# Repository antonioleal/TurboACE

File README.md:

# TurboACE

A hardware expansion for the standard Jupiter Ace, built around a Tang Nano 20K FPGA
module. The same module can also be a complete Jupiter Ace on its own (see
[Two builds](#two-builds-expansion-and-standalone)). It adds:

- 512K of paged RAM (64 × 8K pages, two windows);
- a 256×192 hi-res bitmap with 8×1 colour;
- colour text, 32 text pages and 32 character sets;
- HDMI output, with AY sound carried over HDMI;
- SD card storage: programs as tape files, RAM pages, screens and fonts;
- an extension ROM with new Forth words.

Original Jupiter Ace software keeps working.

The design is in [`register-map.md`](register-map.md) and the ROM source in [`rom/`](rom/README.md).
The SD card firmware (for the soft CPU in the FPGA) is in [`firmware/`](firmware/README.md),
and the FPGA design (being written) in [`fpga/`](fpga/README.md).
The tests are in [`test/`](test/).
`./build.sh /path/to/ace.rom` builds everything into `release/`, one folder per build
(`release/standalone/`, `release/expansion/`) with the files written into the module (the
bitstream, with the soft CPU's firmware inside, and the ROM pages for its flash) and a
`LOAD.txt` saying how. It fetches the RISC-V compiler with
`./download_toolchain.sh` the first time; the bitstream needs Gowin EDA in
`toolchain/gowim`. Third-party components and their notices are listed in
[`THIRD-PARTY.md`](THIRD-PARTY.md).

## Two builds: Expansion and Standalone

TurboACE comes as two FPGA bitstreams, made from the same design. Which one the module
runs depends only on what was last written into it:

- **Expansion:** the module sits on a small adapter board plugged into a real Jupiter
  Ace's edge connector. The Ace's own Z80, keyboard and cassette are used; TurboACE
  adds memory, graphics, sound, HDMI and the SD card.
- **Standalone:** no Jupiter Ace is needed. The whole Ace (Z80, memory, keyboard port,
  beeper, 50 Hz interrupt) is inside the FPGA, with a PS/2 keyboard and the SD card as
  the only tape. It runs the same software at the same speed (3.25 MHz, with the stock
  screen-access timing), plus everything TurboACE adds.

|  | Expansion | Standalone |
|---|---|---|
| Needs | a Jupiter Ace, the adapter board, the Tang Nano 20K | the Tang Nano 20K, a PS/2 keyboard and adapter |
| Z80 | the Ace's own | inside the FPGA (T80 core) |
| Keyboard | the Ace's own | PS/2, translated to the Ace's keys (below) |
| Tape | the Ace's cassette port, or the SD card with `SDTAPE` | the SD card only (`SDTAPE` is always on) |
| Display and sound | HDMI (TurboACE's screens and AY sound) | HDMI (screen, AY sound and the beeper) |
| Without `/ace.rom` | the Ace starts on its own ROM, as a stock Ace | `TURBOACE: CANNOT START` on the screen, tries again every second |

**Changing build** means writing the other bitstream into the module through its USB
port with [openFPGALoader](https://github.com/trabucayre/openFPGALoader); nothing else
changes. Both builds also need TurboACE's own ROM pages in the module's flash, written
once (see [`rom/`](rom/README.md)):

```
make program BUILD=standalone ACE_ROM=/path/to/ace.rom   # bitstream and ROM pages
make program-bitstream BUILD=expansion                   # later: change build only
```

`ACE_ROM` is only used to build the ROM pages; the stock ROM itself is not written to
the board. `make load BUILD=...` loads a bitstream until power-off, for testing, and
`FPGALOADER=echo` shows the commands without running them. The targets are in the
top-level [`Makefile`](Makefile).

### Installing the standalone build

**You need:**

- the Tang Nano 20K and a USB-C cable (it powers and programs the module);
- a PS/2 keyboard and the small PS/2 adapter ([The keyboard](#the-keyboard-standalone) below);
- an HDMI display that accepts 720×576 at 50 Hz (most TVs and many monitors);
- a microSD card, FAT32, holding your copy of the stock ROM as `/ace.rom`
  ([The SD card](#the-sd-card) below);
- on the PC: [openFPGALoader](https://github.com/trabucayre/openFPGALoader).

**The files** are in `release/standalone/`, made by `./build.sh /path/to/ace.rom` (it
needs Gowin EDA in `toolchain/gowim` for the bitstream; see [`INDEX.md`](INDEX.md)):
`turboace-standalone.fs` (the bitstream) and `turboace-flash.bin` (TurboACE's ROM pages).
Its `LOAD.txt` has the same commands as below.

**Steps:**

1. **Prepare the card:** format it FAT32 and copy the stock ROM to it as `/ace.rom`.
   Programs go in `/programs`.
2. **Wire the keyboard** through the level shifter to FPGA pins **73** (clock) and
   **74** (data), the first two pins of the module's left header at the USB end, with
   5 V and ground, as in the table below. Plug in the display.
3. **Connect the module** to the PC by USB. Check that openFPGALoader sees it:
   ```
   openFPGALoader --detect -b tangnano20k
   ```
   If it says it cannot open the device, your user may not have access to the USB
   port: run the command as root once, or allow it permanently with a udev rule
   (the module's USB ID is `0403:6010`), then unplug and replug the module:
   ```
   # /etc/udev/rules.d/99-tangnano20k.rules
   SUBSYSTEM=="usb", ATTRS{idVendor}=="0403", ATTRS{idProduct}=="6010", MODE="0666"
   ```
   ```
   udevadm control --reload-rules && udevadm trigger
   ```
4. **Write TurboACE's ROM pages** into the module's flash (once; both builds use them):
   ```
   make program-rom ACE_ROM=/path/to/ace.rom
   ```
   or, from `release/standalone/`:
   `openFPGALoader -b tangnano20k --external-flash -o 0x500000 turboace-flash.bin`
5. **Try the bitstream** without writing it to flash; it is lost at power-off:
   ```
   make load BUILD=standalone
   ```
   With the card in, the Jupiter Ace's screen and prompt appear on the display within
   a second.
6. **Write it to flash** so the module starts as a Jupiter Ace at every power-up:
   ```
   make program-bitstream BUILD=standalone
   ```
   or, from `release/standalone/`: `openFPGALoader -b tangnano20k -f turboace-standalone.fs`

`make program BUILD=standalone ACE_ROM=/path/to/ace.rom` does steps 4 and 6 together.
Button **S1** on the module resets everything (as a power-up); **Ctrl + Alt + Del**
resets only the Ace.

**The module's LEDs** (on when lit) show how far it got:

| LED (pin) | On means |
|---|---|
| 0 (15) | the Z80 is running |
| 1 (16) | the ROM is loaded (from `/ace.rom` and the flash) |
| 2 (17) | the SD card has been used |
| 3 (18) | the picture fell behind (should never light) |

**If something is wrong:**

- *No picture:* check the display accepts 720×576 at 50 Hz. If LEDs 0 and 1 are on, the
  Ace is running and the fault is in the HDMI output; this first bitstream has not yet
  been tried on a board, so please report it.
- *`TURBOACE: CANNOT START` on the screen:* `/ace.rom` is missing or not the stock ROM
  (it must be 8,192 bytes, MD5 `db6efdfd82cebdfbb493d85b1a5efc3c`). TurboACE tries again
  every second, so fixing the card is enough.
- *LED 1 stays off:* the card is not read: check it is FAT32 and fully inserted, and that
  step 4 was done.
- *The keyboard does nothing:* check the level shifter's wiring and its 5 V and 3.3 V
  supplies; data and clock must not be swapped.

### The SD card

**The card must hold `/ace.rom`**, your own copy of the stock Jupiter Ace ROM (8,192
bytes, MD5 `db6efdfd82cebdfbb493d85b1a5efc3c`). TurboACE does not include it: at power-up
it reads it from the card, checks it, and builds its ROM from it. If it is missing or
different, the standalone build says why on the screen and starts as soon as the card is
right; the expansion leaves the Ace to start on its own ROM, as a plain stock Ace.

The SD words start in the folder `/programs`; see [SD card](#sd-card) below.

### The keyboard (standalone)

A PC keyboard with a PS/2 connector plugs into a small PS/2 adapter next to the module.
The keyboard works at 5 V and the FPGA at 3.3 V, so the clock and data lines go through
a bidirectional level shifter (one small MOSFET and two pull-up resistors per line):

| PS/2 socket pin | Signal | Goes to |
|---|---|---|
| 1 | data | level shifter, 5 V side → 3.3 V side → FPGA pin 74 (left header, pin 2) |
| 3 | ground | GND |
| 4 | +5 V | the module's 5 V pin (from USB) |
| 5 | clock | level shifter, 5 V side → 3.3 V side → FPGA pin 73 (left header, pin 1) |
| 2, 6 | — | not connected |

The full parts list and wiring are in
[`hardware/standalone-carrier.md`](hardware/standalone-carrier.md).

The keyboard has two modes; **Scroll Lock** switches between them, and its
light is on in positional mode.

- **Symbolic** (at power-up): a key types what is printed on it. PC `=` gives `=`, even
  though the Ace types it with SYMBOL SHIFT + L. Best for typing programs.
- **Positional:** the keys act as the Ace's keys in the same place. Shift is SHIFT and
  Ctrl is SYMBOL SHIFT. Best for games.

These keys work in both modes:

| PC key | Ace key | Does |
|---|---|---|
| Backspace, Delete | SHIFT + 0 | delete |
| ← ↑ ↓ → | SHIFT + 5 / 6 / 7 / 8 | move the cursor |
| Esc | SHIFT + SPACE | BREAK |
| Caps Lock | SHIFT + 2 | caps lock (the light follows) |
| Tab | SHIFT + 1 | delete line |
| F4 | SHIFT + 4 | inverse video on/off |
| F9 | SHIFT + 9 | graphics on/off |
| Ctrl + Alt + Del | | reset the Ace |

**US and Portuguese layouts.** A settings file on the card, `/turboace.cfg`, chooses the
layout and the starting mode; without it the keyboard is US and symbolic:

```
# /turboace.cfg
keyboard = pt          # us or pt
keymode = symbolic     # symbolic or positional
```

On the Portuguese layout the accent keys (´ ` ~ ^) type their own character at once.
ç, º, ª, «, », £, § and € have no Ace key and type nothing.

## Starting up: `TURBO`

There is no switch. The machine powers up as a **51K Jupiter Ace**, like a stock Ace with
a 48K RAM pack. Only a few new words are visible: `TURBO`, which selects the mode, and the
SD card words `SDTAPE`, `TAPE`, `EJECT`, `DIR`, `CD`, `DELETE` and `SDERR`, so old
programs can be loaded from the card straight away.

| Command | Mode |
|---------|------|
| `1 TURBO` | **TurboACE**: all the words below. The machine stack moves below `$C000`, leaving the paged RAM free. Gives `ERROR 1` if the dictionary is too close to `$C000` |
| `0 TURBO` | **51K Ace** (the power-up mode): only `TURBO` and the SD card words visible, stock text screen, white on black |
| `-1 TURBO` | **Stock Ace with the card, until reset**: the stock words only and the `$3000` mirror of the system variables, but the tape words keep using the card (the tape chosen before, with `SDTAPE` on). See [The SD card in `-1 TURBO`](#the-sd-card-in--1-turbo) |
| `-2 TURBO` | **Completely stock Ace until reset**: the original ROM, byte for byte, the whole `$3000` mirror and the real cassette. For software that needs an untouched machine |

`TURBO` ends like `QUIT`. The dictionary and the data stack are kept, but the rest of the
input line is not run, so use it on a line of its own or as the last word of a program.

```
1 TURBO
1 MODE CLS 128 96 50 CIRCLE
```

Both builds start this way, once `/ace.rom` is on the card
([The SD card](#the-sd-card)).

## New Forth words

After `1 TURBO`, the words below are added to the `FORTH` vocabulary. Your own words keep
working alongside them.

**Conventions**

- **Stack effects** are written `( before -- after )`, as in the Ace manual.
- **Hi-res coordinates** are `x` 0–255 (left to right) and `y` 0–191 (bottom to top).
  The origin is the bottom-left corner.
- **Colours** are numbers 0–15, given by name with the colour constants below.
- **Examples** assume `1 TURBO` has been typed. Loops (`DO … LOOP`) and `."` are used
  inside colon definitions, as the Ace requires.

> Word addresses are not frozen yet. Programs saved with this ROM may need recompiling
> after a ROM update.

### Quick reference

| Group | Words |
|-------|-------|
| Mode | `TURBO` |
| Utilities | `COUNT` `+!` `?` `DEPTH` `HEX` `CMOVE` `FILL` |
| Programming | `.S` `'` `2*` `2/` `0<>` `CASE` `OF` `ENDOF` `ENDCASE` `RND` `RAND` `GR` |
| Double numbers | `2DUP` `2DROP` `2SWAP` `2OVER` `2ROT` `D.` `D.R` `D-` `D=` `D0=` `DABS` `S->D` |
| Floating point | `PI` `FSQRT` `FSIN` `FCOS` `FTAN` `FABS` `F<` `F>` `F0<` `F0=` |
| Sound | `PLAY!` `PLAY@` |
| Colour | `INK` `PAPER` `BORDER` `DARK` `BLACK` `GREY` `BLUE` `GREEN` `CYAN` `RED` `PURPLE` `YELLOW` `WHITE` |
| Screens and memory | `MODE` `PG0` `PG1` `FONT` `VIEW` `WORK` `SCREEN` |
| Graphics | `PLOT` `DRAW` `CIRCLE` `PAINT` `POINT` `ATTR` `INVERSE` `FLIP` `CLS` `OPAQUE` |
| SD card | `SDTAPE` `TAPE` `EJECT` `DIR` `CD` `DELETE` `PGSAVE` `PGLOAD` `SCRSAVE` `SCRLOAD` `FONTLOAD` `SDERR` |

### Mode

| Word | What it does |
|------|--------------|
| `TURBO` | Select the mode: `1` TurboACE, `0` 51K Ace, `-1` stock Ace with the card, `-2` completely stock Ace (both until reset) |

#### `TURBO` `( n -- )`

Selects the machine's mode, described in [Starting up](#starting-up-turbo) above.
At power-up only `TURBO` and the SD card words are visible.

- `1 TURBO`: all the new words.
- `0 TURBO`: back to a plain 51K Ace, with the SD card words.
- `-1 TURBO`: a stock Ace until the next reset, whose tape words still use the card.
- `-2 TURBO` (or any lower number): a completely stock Ace until the next reset.

`TURBO` restarts the interpreter like `QUIT`, so make it the last word on a line.

```
1 TURBO
```

### Utilities

| Word | What it does |
|------|--------------|
| `COUNT` | Turn a counted string's address into address and length |
| `+!` | Add a number to a variable |
| `?` | Print a variable's value |
| `DEPTH` | Count the items on the data stack |
| `HEX` | Switch number input and output to base 16 |
| `CMOVE` | Copy a block of memory (overlap-safe) |
| `FILL` | Fill a block of memory with one byte |

#### `COUNT` `( addr -- addr+1 n )`

Turns the address of a *counted string* (a length byte followed by the characters) into
the address and length that `TYPE` expects.

```
CREATE GREETING 5 C, 72 C, 69 C, 76 C, 76 C, 79 C,
GREETING COUNT TYPE
```

This prints `HELLO`.

#### `+!` `( n addr -- )`

Adds `n` to the number stored at `addr`. It is handy for counters and scores.

```
0 VARIABLE SCORE
: HIT 10 SCORE +! ;
HIT HIT HIT SCORE ?
```

This prints `30`.

#### `?` `( addr -- )`

Prints the number stored at `addr`. It is short for `@ .`.

```
SCORE ?
```

#### `DEPTH` `( -- n )`

The number of items on the data stack, without changing them. Useful for checking that a
word leaves the stack as expected.

```
1 2 3 DEPTH .
```

This prints `3`, and `1 2 3` are still on the stack.

#### `HEX` `( -- )`

Switches number input and output to base 16. `DECIMAL` (a stock word) switches back.
Addresses are easier to write in hex.

```
HEX 2400 DECIMAL .
```

This prints `9216`, the address of the text screen.

#### `CMOVE` `( from to n -- )`

Copies `n` bytes from address `from` to address `to`. The areas may overlap: `CMOVE`
chooses the copy direction so that nothing is overwritten before it is copied. This example
keeps a copy of the text screen in RAM page 4. The second line, typed later, brings it back.

```
4 PG0  HEX 2400 C000 300 CMOVE DECIMAL
4 PG0  HEX C000 2400 300 CMOVE DECIMAL
```

The text screen is `$300` (768) bytes at `$2400`. Characters copied back to the screen take
the current `INK` and `PAPER`.

#### `FILL` `( addr n byte -- )`

Sets `n` bytes, starting at `addr`, to `byte`. This is the memory fill; the graphics flood
fill is `PAINT`.

```
HEX 2400 300 DECIMAL 42 FILL
```

This fills the whole text screen with `*` (character 42) in the current colours.

```
5 PG0  HEX C000 2000 0 FILL DECIMAL
```

This clears all of RAM page 5 (8K).

### Programming

| Word | What it does |
|------|--------------|
| `.S` | Print the whole data stack without changing it |
| `'` | The parameter field of the next word (a variable's address) |
| `2*` | Multiply by 2 |
| `2/` | Divide by 2, rounding down |
| `0<>` | 1 if a number is not zero |
| `CASE` `OF` `ENDOF` `ENDCASE` | Choose between several cases by value |
| `RND` | A random number from 0 to n−1 |
| `RAND` | Start the random numbers from a seed |
| `GR` | Define the shape of a character |

#### `.S` `( -- )`

Prints every item on the data stack, the oldest first, and leaves them all there. Use it
while trying out words, to see what they leave behind.

```
1 2 3 .S
```

This prints `1 2 3`, and the three numbers are still on the stack. With an empty stack
`.S` prints nothing.

#### `'` `( -- addr )`

`' name` gives the parameter field of the word `name`: for a `VARIABLE` that is its
address, for a `CONSTANT` the place where its value is kept. Words that are not in the
dictionary give `ERROR 13`.

```
5 VARIABLE LIVES
' LIVES ?
```

This prints `5`.

#### `2*` `( n -- 2n )` · `2/` `( n -- n/2 )`

Fast multiply and divide by 2. `2/` shifts, so it rounds down: `-3 2/` gives `-2`.

```
5 2* .   -3 2/ .
```

This prints `10 -2`.

#### `0<>` `( n -- f )`

1 if `n` is not zero, 0 if it is. Handy in `IF` and `UNTIL` tests.

```
0 0<> .   9 0<> .
```

This prints `0 1`.

#### `CASE` `OF` `ENDOF` `ENDCASE`

Choose what to do from a value, instead of a chain of `IF`s. Used inside colon
definitions:

```
: SPELL ( n -- )
  CASE
    1 OF ." ONE " ENDOF
    2 OF ." TWO " ENDOF
    ." MANY " ( n is still on the stack here )
  ENDCASE ;
1 SPELL  2 SPELL  7 SPELL
```

This prints `ONE TWO MANY`.

- `CASE` takes the value to test.
- Each `v OF … ENDOF` runs its words when the value equals `v`, then continues after
  `ENDCASE`. The value is dropped before the words run.
- Words between the last `ENDOF` and `ENDCASE` run when no `OF` matched; the value is
  still on the stack there, and `ENDCASE` drops it.
- `CASE` can be nested. A wrong order (for example `ENDOF` without `OF`) gives
  `ERROR 5`, as an `IF` without `THEN` does.
- `LIST` and `EDIT` show them like `IF` and `THEN`.

#### `RND` `( n -- r )` · `RAND` `( n -- )`

`RND` gives a random number from 0 to `n`−1 (`0 RND` gives 0). `RAND` sets where the
sequence starts: the same seed always gives the same numbers, which helps when testing a
game; `0 RAND` takes the seed from the frame counter, so each run is different.

```
0 RAND
: DICE 6 RND 1+ ;
DICE .  DICE .  DICE .
```

This prints three throws of a die. The sequence repeats only after 65,536 numbers.

#### `GR` `( b1 b2 b3 b4 b5 b6 b7 b8 c -- )`

Defines the shape of character `c` (0–127) from eight bytes, `b1` the top row. Each bit
set is an INK pixel, bit 7 on the left. It changes the character set being written,
chosen with `FONT`.

```
HEX 18 3C 7E DB FF 24 5A A5 DECIMAL 127 GR
127 EMIT
```

This turns character 127 into a small invader and prints it. Hex is easier than decimal
for row patterns: each hex digit is four pixels. Character `c + 128` shows the same shape
inverted.

### Double numbers

| Word | What it does |
|------|--------------|
| `2DUP` | Copy a double number (or a floating-point number) |
| `2DROP` | Drop a double number |
| `2SWAP` | Swap two double numbers |
| `2OVER` | Copy the second double number to the top |
| `2ROT` | Bring the third double number to the top |
| `D.` | Print a double number |
| `D.R` | Print a double number right-aligned in a field |
| `D-` | Subtract double numbers |
| `D=` | 1 if two double numbers are equal |
| `D0=` | 1 if a double number is zero |
| `DABS` | Absolute value of a double number |
| `S->D` | Turn a number into a double number |

A double number takes two stack cells, the high part on top, and holds values up to about
±2,000 million. The stock words `U*`, `D+`, `D<`, `DNEGATE` and `U/MOD` make and use
them. A floating-point number also takes two cells, so the `2…` words move those too.

#### `2DUP` `2DROP` `2SWAP` `2OVER` `2ROT`

The stack words `DUP`, `DROP`, `SWAP`, `OVER` and `ROT`, for pairs of cells:
`( d -- d d )`, `( d -- )`, `( d1 d2 -- d2 d1 )`, `( d1 d2 -- d1 d2 d1 )` and
`( d1 d2 d3 -- d2 d3 d1 )`.

```
1.5 2DUP F* F.
```

This prints `2.25`.

#### `D.` `( d -- )` · `D.R` `( d n -- )`

`D.` prints a double number and a space, like `.`. `D.R` prints it right-aligned in `n`
characters, which lines up columns; a number too wide for the field is printed whole.

```
1000 1000 U* D.
-1234 S->D 8 D.R
```

This prints `1000000`, then `-1234` after four spaces.

#### `D-` `( d1 d2 -- d )` · `D=` `( d1 d2 -- f )` · `D0=` `( d -- f )`

Subtraction and tests for double numbers (`D+` and `D<` are stock words).

```
1000 1000 U*  999 1000 U*  D- D.
```

This prints `1000`.

#### `DABS` `( d -- |d| )` · `S->D` `( n -- d )`

`DABS` removes the sign of a double number; `S->D` turns a number into a double number
with the same value.

```
-5 S->D DABS D.
```

This prints `5`.

### Floating point

| Word | What it does |
|------|--------------|
| `PI` | The number π, 3.14159 |
| `FSQRT` | Square root |
| `FSIN` `FCOS` `FTAN` | Sine, cosine and tangent of an angle in radians |
| `FABS` | Absolute value |
| `F<` `F>` | Compare two floating-point numbers |
| `F0<` `F0=` | Test a floating-point number for negative or zero |

The Ace's floating-point numbers (typed with a decimal point, like `1.5`) have six
digits; the stock words `F+` `F-` `F*` `F/` `FNEGATE` `F.` `INT` and `UFLOAT` work on
them. These words add the functions. Use `2DUP` `2DROP` `2SWAP` `2OVER` to move them on
the stack.

#### `PI` `( -- f )`

```
2. PI F* F.
```

This prints `6.28318`, the length of a circle of radius 1.

#### `FSQRT` `( f -- r )`

The square root, to all six digits. A negative number gives `ERROR 8`, the Ace's
floating-point error.

```
2. FSQRT F.   1.E6 FSQRT F.
```

This prints `1.41422 1000.`.

#### `FSIN` `( x -- f )` · `FCOS` `( x -- f )` · `FTAN` `( x -- f )`

Sine, cosine and tangent of `x` radians (degrees × `PI` / 180). They are good to about
five digits for angles up to a few turns; for very large angles (thousands of radians)
the six-digit numbers lose precision. `x` must be less than about 200,000. The tangent of
a right angle gives `ERROR 8`.

```
: DEG PI F* 180. F/ ;
30. DEG FSIN F.   60. DEG FCOS F.   45. DEG FTAN F.
```

This prints `.499999 .500001 1.00001`: right to within a few millionths.

#### `FABS` `( f -- |f| )` · `F<` `( f1 f2 -- flag )` · `F>` `( f1 f2 -- flag )`

`FABS` removes the sign. `F<` gives 1 if `f1` is less than `f2`, `F>` if it is greater.

```
-2.5 FABS F.   1. 2. F< .
```

This prints `2.5 1`.

#### `F0<` `( f -- flag )` · `F0=` `( f -- flag )`

1 if `f` is negative, or zero.

```
-.5 F0< .   0. F0= .
```

This prints `1 1`.

### Sound

| Word | What it does |
|------|--------------|
| `PLAY!` | Write an AY sound register |
| `PLAY@` | Read an AY sound register |

TurboACE has an AY-3-8910-compatible sound generator, built into its FPGA and heard
through the HDMI output. It behaves like a real AY-3-8910 clocked at 3.25 MHz.

- **Registers 0–13** make sound: three tone channels, noise and an envelope.
- **Registers 14 and 15** carry the colours, so leave them to `INK`, `PAPER` and `BORDER`.

#### `PLAY!` `( value reg -- )`

Writes `value` to AY register `reg`.

A tone's frequency is 3,250,000 / (16 × period), where the period is held in registers 0
(low byte) and 1 (high byte) for channel A. Register 8 is channel A's volume (0–15), and
register 7 switches channels on.

Register 7's top two bits don't affect the colours on TurboACE, but keeping them set
(values of 192 or more, as in the example) stays compatible with a real AY.

```
: TONE ( period -- ) 256 /MOD 1 PLAY! 0 PLAY! 15 8 PLAY! 254 7 PLAY! ;
: QUIET 0 8 PLAY! ;
203 TONE
```

`203 TONE` plays about 1 kHz on channel A until `QUIET`. A larger period gives a lower note.

#### `PLAY@` `( reg -- value )`

Reads AY register `reg`.

```
8 PLAY@ .
```

This prints channel A's volume.

### Colour

| Word | What it does |
|------|--------------|
| `INK` | Set the colour of text and drawing |
| `PAPER` | Set the background colour |
| `BORDER` | Set the border colour |
| `DARK` | Turn a colour into its dark version |
| `BLACK` `GREY` `BLUE` `GREEN` `CYAN` `RED` `PURPLE` `YELLOW` `WHITE` | Colour constants (0, 8–15) |

Colours are numbers 0–15. Bit 3 is the intensity (bright), and bits 2, 1 and 0 are red,
green and blue:

| Number | Colour | Number | Colour |
|--------|--------|--------|--------|
| 0 | black | 8 | `GREY` |
| 1 | dark blue | 9 | `BLUE` |
| 2 | dark green | 10 | `GREEN` |
| 3 | dark cyan | 11 | `CYAN` |
| 4 | dark red | 12 | `RED` |
| 5 | dark purple | 13 | `PURPLE` |
| 6 | dark yellow (brown) | 14 | `YELLOW` |
| 7 | light grey | 15 | `WHITE` |

**Text colour:**

- **Each character cell has its own colours,** taken from `INK` and `PAPER` when the
  character is written.
- **Changing colour doesn't affect what is already on screen.** `CLS` repaints every cell
  in the current colours.

**Hi-res:** the drawing words paint every 8-pixel colour cell they touch in the current
`INK` and `PAPER`.

#### `INK` `( c -- )` · `PAPER` `( c -- )` · `BORDER` `( c -- )`

Set the colour of the characters and lines (`INK`), of their background (`PAPER`), and of
the screen border (`BORDER`).

```
: TITLE  BLUE PAPER CLS  RED BORDER
  YELLOW INK ." TURBOACE"  WHITE INK ;
TITLE
```

This shows a blue screen with a red border and yellow text, and leaves white ink for what
follows.

#### `DARK` `( c -- c' )`

Gives the dark version of a colour by clearing its intensity bit. Use it with the colour
constants to reach colours 0–7.

```
RED DARK INK
```

This selects dark red ink (colour 4). `GREY DARK` is black.

#### `BLACK` `GREY` `BLUE` `GREEN` `CYAN` `RED` `PURPLE` `YELLOW` `WHITE` `( -- c )`

Colour constants: 0, 8, 9, 10, 11, 12, 13, 14 and 15.

```
WHITE INK BLACK PAPER BLACK BORDER CLS
```

This restores the power-up colours.

### Screens and memory

| Word | What it does |
|------|--------------|
| `MODE` | Switch between text (`0`) and hi-res (`1`) |
| `PG0` | Show an 8K RAM page at `$C000–$DFFF` |
| `PG1` | Show an 8K RAM page at `$E000–$FFFF` |
| `FONT` | Select one of 32 character sets |
| `VIEW` | Choose the screen that is shown |
| `WORK` | Choose the screen that is printed and drawn on |
| `SCREEN` | Choose the screen that is shown and written (`VIEW` + `WORK`) |

#### `MODE` `( n -- )`

- `0 MODE`: the stock 32×24 text screen.
- `1 MODE`: the 256×192 hi-res screen, with the text shown on top of it (see
  [Text in hi-res](#text-in-hi-res)).

Switching mode doesn't clear anything, so follow `1 MODE` with `CLS` the first time.

```
1 MODE CLS
128 96 40 CIRCLE
0 MODE
```

The circle is kept, and is there again after the next `1 MODE`.

#### `PG0` `( p -- )` · `PG1` `( p -- )`

TurboACE has 512K of extra RAM, as 64 pages of 8K. Two windows each show one page:

- `p PG0` shows page `p` at `$C000–$DFFF`;
- `p PG1` shows page `p` at `$E000–$FFFF`.

After `1 TURBO` this area holds only your data. The graphics words borrow both windows
while they draw, and always restore your pages.

```
10 PG0  HEX 1234 C000 ! DECIMAL
11 PG0  HEX C000 @ . DECIMAL
10 PG0  HEX C000 @ . DECIMAL
```

The first `.` prints whatever page 11 holds. The second prints `1234` again from page 10.

```
10 PG0  20 PG1  HEX C000 E000 2000 CMOVE DECIMAL
```

This copies all of page 10 into page 20.

Hi-res screen `n` uses pages `2n` and `2n+1` (screen 0 uses pages 0 and 1). Keep your data
in pages that your screens don't use.

#### `FONT` `( n -- )`

Selects character set `n` (0–31), both for the screen and for redefining characters.

- **Set 0** is the standard character set.
- **Sets 1–31 are not set up at power-up.** Define every character you will use before
  showing one.
- **Character data:** a character's eight rows of pixels go at
  `11264 + 8 × code`, top row first.
- **The character memory can be written but not read back.**

```
: SMILE  60 66 153 165 129 165 66 60  11552 11544 DO I C! LOOP ;
: DEMO  1 FONT  11264 1024 0 FILL  SMILE  CLS ." ###"
  BEGIN INKEY 0= UNTIL  BEGIN INKEY UNTIL  0 FONT ;
DEMO
```

`SMILE` stores a smiling face as character 35 (`#`) in the current font. Its eight rows are
listed bottom row first, because the loop stores the last number pushed first.

`DEMO` selects font 1 and blanks it, so nothing undefined shows. It adds the face, and
prints three faces until a key is pressed. Then `0 FONT` brings back the standard set, and
the same cells show `###`.

#### `VIEW` `( n -- )` · `WORK` `( n -- )` · `SCREEN` `( n -- )`

There are 32 screens, numbered 0–31. Each one has a text page, and in hi-res also a
picture.

- `n VIEW` chooses the screen that is **shown**.
- `n WORK` chooses the screen that is **written**: printing goes to its text page and
  drawing to its picture.
- `n SCREEN` does both.

Drawing on a screen that isn't shown, then showing it, gives flicker-free animation:

```
: SHOW ( n -- ) DUP WORK CLS  DUP 10 * 20 + 128 96 ROT CIRCLE  VIEW ;
1 MODE  1 SHOW  2 SHOW  3 SHOW  0 SCREEN
```

Each `SHOW` draws a circle on a hidden screen and then shows it.

There is one print position, shared by all the text pages. While `WORK` and `VIEW` differ,
what you type goes to the hidden page, so end with `n SCREEN` before returning to the
keyboard.

### Graphics

| Word | What it does |
|------|--------------|
| `PLOT` | Plot, unplot, invert or move to a point |
| `DRAW` | Draw a line or an arc from the current position |
| `CIRCLE` | Draw a circle |
| `PAINT` | Fill an enclosed area |
| `POINT` | Test whether a pixel is set |
| `ATTR` | Read the colour at a pixel or character cell |
| `INVERSE` | Make drawing erase instead of draw |
| `FLIP` | Make drawing invert pixels |
| `CLS` | Clear the screen (picture and text in hi-res) |
| `OPAQUE` | Make text over a hi-res picture transparent or opaque |

`DRAW`, `CIRCLE`, `PAINT` and `POINT` work in hi-res (`1 MODE`) only. In text mode they
do nothing, and `POINT` returns 0. `PLOT`, `CLS` and `ATTR` work in both modes.

#### `PLOT` `( x y n -- )`

Plots one point and sets the position that `DRAW` starts from. `n` selects what happens
to the pixel:

| `n` | Effect |
|-----|--------|
| 0 | unplot (clear) |
| 1 | plot (set) |
| 2 | move only |
| 3 | invert |

In text mode, `PLOT` is the stock 64×48 block `PLOT`. In hi-res, points off the screen are
ignored.

```
: DOTS 256 0 DO I 96 1 PLOT 4 +LOOP ;
1 MODE CLS DOTS
```

This draws a dotted line across the middle of the screen.

#### `DRAW` `( dx dy a -- )`

Draws from the current position to a point `dx` across and `dy` up from it, and moves the
position there. `a` is the angle to turn through on the way, in degrees:

| `a` | Line drawn |
|-----|------------|
| 0 | straight line |
| positive | arc turning anticlockwise (to the left) |
| negative | arc turning clockwise |

Parts outside the screen are not drawn, and the position stops at the screen edge.

```
: BOX  40 40 1 PLOT  100 0 0 DRAW  0 100 0 DRAW  -100 0 0 DRAW  0 -100 0 DRAW ;
: BOWL 150 140 1 PLOT  80 0 180 DRAW ;
1 MODE CLS BOX BOWL
```

`BOX` draws a square. `BOWL` draws a half circle hanging below a line 80 pixels wide.

#### `CIRCLE` `( x y r -- )`

Draws a circle with centre `x y` and radius `r`. Parts outside the screen are not drawn,
and the `DRAW` position is not changed.

```
: RINGS 90 10 DO 128 96 I CIRCLE 10 +LOOP ;
1 MODE CLS RINGS
```

This draws eight circles around the centre.

#### `PAINT` `( x y -- )`

Fills the area around `x y` with `INK`. Outlines drawn with `DRAW` and `CIRCLE` are closed
for `PAINT`, so the fill never leaks out through their diagonal steps.

- **With `1 INVERSE`, `PAINT` erases** an area of set pixels instead.
- **It gives `ERROR 1` if it runs out of memory.** This can happen with very complicated
  shapes and little free memory.
- **Speed:** a full screen takes about 1.4 seconds. Shapes broken up by many small gaps
  are slower.

```
: HOUSE  CYAN INK
  60 40 1 PLOT  100 0 0 DRAW  0 70 0 DRAW  -100 0 0 DRAW  0 -70 0 DRAW
  60 110 2 PLOT  50 50 0 DRAW  50 -50 0 DRAW
  RED INK 100 70 PAINT  YELLOW INK 110 130 PAINT ;
1 MODE CLS HOUSE
```

The walls are a box. `60 110 2 PLOT` moves to the top-left corner without drawing, and the
roof is two lines meeting at the top. The walls are then filled red and the roof yellow.

Colour belongs to 8-pixel cells, so parts of the cyan outline that share a cell with the
fill take the fill's colour.

#### `POINT` `( x y -- f )`

Returns 1 if the pixel at `x y` is set (INK), or 0 if it is clear or off the screen. Use it
to test for collisions.

```
: HIT? ( x y -- ) POINT IF ." BANG" THEN ;
1 MODE CLS  128 96 1 PLOT  128 96 HIT?
```

This prints `BANG`.

#### `ATTR` `( x y -- c )`

Returns a colour byte, PAPER × 16 + INK, or 0 if `x y` is out of range.

- **Hi-res:** the colour of the 8-pixel cell that holds pixel `x y`.
- **Text mode:** the colours of the character at column `x` (0–31) and line `y` (0–23,
  counted from the top).

```
128 96 ATTR 16 /MOD . .
```

This prints the PAPER, then the INK, at the centre of the screen.

#### `INVERSE` `( f -- )` · `FLIP` `( f -- )`

Change how `DRAW`, `CIRCLE` and `PAINT` affect pixels until you change them back:

| | `0 FLIP` | `1 FLIP` |
|---|---|---|
| `0 INVERSE` | draw (set pixels, the normal case) | invert pixels |
| `1 INVERSE` | erase (clear pixels) | move only, draw nothing |

`FLIP` flips each pixel it touches. Inverting is useful for moving
shapes: drawing the same shape twice with `1 FLIP` removes it and leaves the background
as it was. `PLOT` ignores both settings, because its `n` already selects the effect.

```
: RING 128 96 30 CIRCLE ;
1 MODE CLS RING
1 INVERSE RING 0 INVERSE
1 FLIP RING RING 0 FLIP
```

The second line erases the ring. In the third line the ring appears and disappears again.

#### `CLS` `( -- )`

Clears the screen.

- **Text mode:** the stock `CLS`.
- **Hi-res:** clears the picture of the `WORK` screen to the current `PAPER` and `INK`,
  moves the `DRAW` position to 0,0, and clears the text on top of it.

```
1 MODE  BLUE PAPER WHITE INK CLS
```

This gives an empty blue hi-res screen.

#### `OPAQUE` `( f -- )`

Sets how text looks over a hi-res picture:

- `0 OPAQUE` (the default): only the letters cover the picture.
- `1 OPAQUE`: each character also covers its 8×8 cell in its `PAPER` colour, which is
  easier to read over a busy picture.

Spaces never cover the picture.

```
: BUSY 192 0 DO 0 I 1 PLOT 255 0 0 DRAW 4 +LOOP ;
: LABEL BLACK PAPER YELLOW INK ." SCORE 100" ;
1 MODE CLS BUSY  1 OPAQUE LABEL
```

The label sits on a solid black strip over the striped picture.

### Text in hi-res

In `1 MODE` the text screen is shown on top of the picture, so `."`, `.`, the input line and
the cursor all stay visible, each character in the colours it was printed with. Spaces
are transparent, so after `CLS` the whole picture shows. With `1 OPAQUE`, each printed
character also covers its 8×8 cell with its PAPER colour, which keeps text readable over
busy pictures.

### Example: a filled, outlined disc with an arch

```
: DISC ( -- )
  1 MODE  BLACK PAPER  CLS
  YELLOW INK  128 96 60 CIRCLE  128 96 PAINT
  RED INK     128 96 60 CIRCLE
  WHITE INK   68 96 1 PLOT  120 0 0 DRAW
  GREEN INK   68 96 1 PLOT  120 0 -90 DRAW
  WHITE INK   ." A DISC" ;
DISC
```

The text `A DISC` appears in white over the picture, at the top left after `CLS`.
Type `0 MODE` to go back to text mode.

### SD card

| Word | What it does |
|------|--------------|
| `SDTAPE` | Make the stock tape words use the SD card (`1`) or the real cassette (`0`) |
| `TAPE` | Put a tape file from the card in the virtual tape player |
| `EJECT` | Empty the virtual tape player |
| `DIR` | List the files in the current folder |
| `CD` | Change the current folder |
| `DELETE` | Delete a file |
| `PGSAVE` | Save an 8K RAM page to a file |
| `PGLOAD` | Load an 8K RAM page from a file |
| `SCRSAVE` | Save a hi-res screen (picture and colours) to a file |
| `SCRLOAD` | Load a hi-res screen from a file |
| `FONTLOAD` | Load a character set from a file |
| `SDERR` | The reason for the last SD card error |

The microSD card on the TurboACE module holds an ordinary FAT file system, so a PC can
read and write it too.

- **Names:** words that take a file name read it from the line, like `SAVE name`.
- **Folder:** the current folder starts at `/programs`.
- **Errors:** any failure gives `ERROR 10`, the Ace's tape error. `SDERR` then tells you
  why.

#### `SDTAPE` `( f -- )`

With `1 SDTAPE`, the Ace's own tape words use the card instead of the cassette: `SAVE`,
`LOAD`, `BSAVE`, `BLOAD`, `VERIFY` and `BVERIFY`. Everything you know about them still
applies, but a load takes a moment instead of minutes.

- `0 SDTAPE` goes back to the real cassette, which is also the power-up setting.
- The setting stays after `0 TURBO` and `-1 TURBO`, so a plain 51K Ace, or a stock Ace,
  can load old programs from the card too.

```
1 SDTAPE
SAVE MYGAME
```

With no tape file in the player, this writes `MYGAME.TAP` in the current folder.

#### `TAPE` `( -- )` · `EJECT` `( -- )`

`TAPE name` puts a tape file in the virtual player, at its start, and turns `SDTAPE` on.
It looks for `name`, then `name.TAP`, then `name.TZX`. The tape then behaves like a
cassette:

- **`LOAD name`** searches it for that program. It gives `ERROR 10` after going once
  round the tape without finding it.
- **`LOAD` with no name** lists what is on it.
- **`SAVE`** adds to the end.

`EJECT` takes the tape out. After that, each `SAVE name` writes its own `name.TAP` file.
`TAPE` gives `ERROR 10` if the file isn't on the card, or if the name is missing or
longer than 63 characters. The tape already in the player then stays there.

```
TAPE GAMES
LOAD
LOAD INVADERS
EJECT
```

This lists the programs on `GAMES.TAP`, then loads `INVADERS` from it.

#### `DIR` `( -- )` · `CD` `( -- )` · `DELETE` `( -- )`

- **`DIR`** lists the current folder, one entry per line, folders first. A folder is
  shown with `/` after its name. A file is shown with its size: bytes under 64K,
  `nnnK` from 64K, and `65535K+` from 64 MB up. Holding SPACE stops the listing.
- **`CD name`** moves into a folder. `CD ..` goes up one level, and `CD /` goes to the
  top.
- **`DELETE name`** deletes a file.

`CD` and `DELETE` give `ERROR 10` if the folder or file isn't there; the current folder
stays as it was.

```
DIR
CD GAMES
DELETE OLDTEST.TAP
```

A listing looks like this:

```
DEMOS/
GAMES.TAP 262
MUSIC.TAP 120K
```

#### `PGSAVE` `( p -- )` · `PGLOAD` `( p -- )`

Save RAM page `p` (0–63) to `name.PG`, or load it back. The file holds exactly the
8,192 bytes of the page.

- **A shorter file** loads only the bytes it has; the rest of the page is unchanged.
- **Names:** the name plus `.PG` can be up to 63 characters.
- **Windows:** the words borrow window 0 while they work, and always give back your
  `PG0`/`PG1` pages.

```
10 PGSAVE LEVEL1
10 PGLOAD LEVEL1
```

#### `SCRSAVE` `( n -- )` · `SCRLOAD` `( n -- )`

Save hi-res screen `n` to `name.SCR`, or load it back. The file holds the picture and its
colours (12K), in the screen's own layout.

- **The screen's free 4K** at the end of page `2n+1` is not saved, and `SCRLOAD` leaves it
  alone.
- **Windows:** the words borrow both windows while they work, and give them back.

```
0 SCRSAVE TITLE
0 SCRLOAD TITLE
```

#### `FONTLOAD` `( n -- )`

Loads a character set from `name.FNT` into font `n` (0–31). The file holds 128 characters
of 8 bytes each (1,024 bytes), each character's top row first.

- **The font shown doesn't change:** follow with `n FONT` to use it.
- **A shorter file** loads only the characters it has. There is no `FONTSAVE`, because
the character memory cannot be read back. Keep your font data in RAM, and save it with
`PGSAVE` or `BSAVE`.

```
1 FONTLOAD GOTHIC  1 FONT
```

#### `SDERR` `( -- n )`

The reason for the last SD card failure, or 0 if there has been none since the machine
was switched on. A later success doesn't clear it:

| `n` | Meaning |
|-----|---------|
| 1 | no card |
| 2 | not found |
| 3 | card full |
| 4 | write-protected |
| 5 | read error |
| 6 | bad name |
| 7 | no file open |
| 8 | too large |
| 9 | bad tape block |
| 10 | end of tape |

```
SDERR .
```

### The SD card in `-1 TURBO`

`-1 TURBO` and `-2 TURBO` both make a stock Jupiter Ace until reset: only the stock words,
and `$3000`–`$3BFF` mirrors the system variables again. They differ in the tape:

- **`-1 TURBO`:** the stock ROM with only its two tape hooks (12 bytes). With `SDTAPE` on,
  `LOAD`, `SAVE`, `BLOAD`, `BSAVE`, `VERIFY` and `BVERIFY` use the card, and the tape
  chosen with `TAPE` before the switch, also when a running program calls them; with
  `SDTAPE` off, the real cassette. The last 256 bytes of the mirror (`$3B00`–`$3BFF`) stay
  TurboACE's, for the card's working state. No words are added and no dictionary space is
  used. To change tape, reset: the card words are not there in this mode.
- **`-2 TURBO`:** the original ROM, byte for byte, the whole mirror, and the real cassette
  only.

|  | Expansion | Standalone |
|---|---|---|
| `SDTAPE` at power-up | off (the real cassette) | on, and stays on (no cassette) |
| `-1 TURBO` | the card if `SDTAPE` is on (`1 SDTAPE` or `TAPE name` first), else the real cassette | the card, with the tape chosen before |
| `-2 TURBO` | the real cassette | no tape at all |

```
TAPE GAMES
-1 TURBO
LOAD INVADERS
```

Both stay one-way: only a reset brings TurboACE back.

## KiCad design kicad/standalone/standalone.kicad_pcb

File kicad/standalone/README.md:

# Standalone board (KiCad 10)

The carrier for the standalone build: the Tang Nano 20K plugged into two female
headers, the PS/2 keyboard socket at the board's edge, and the level shifter between the keyboard's 5 V and the FPGA's 3.3 V. KiCad project,
schematic, PCB (footprints placed, outline and design rules set, routed by hand) and
the BoM generated from the schematic. Parts and wiring: ../../hardware/standalone-carrier.md.

Drawn: `standalone.kicad_sch`, `standalone.kicad_pcb`, `standalone.kicad_pro`
(KiCad 10), with `standalone-bom.csv` and `standalone-schematic.pdf`. Made by
`generate.py` (see ../README.md); all its checks pass: the netlist equals the table,
ERC 0, DRC 0 with schematic parity; routed by hand (0 unconnected).

## The board

- 54.04 × 60 mm, flush with the module's ends so the USB-C and HDMI plugs and the
  microSD card (under the USB end) stay reachable; 2 layers.
- The module U1 (locked) on its two sockets, the USB end on the left; its outline on
  F.Fab and its courtyard keep the space under it free. The level shifter module U2
  below U1's J6 row, turned half round so its LV row is the one nearer U1, LV1 at the
  USB end, the HV row below; mounted labelled side up (its BSS138s toward the carrier), as in
  `gebildet-photo.png` (the seller's photo the footprint follows); J3, the PS/2 socket, at the USB edge below U1, its front face on the edge so the keyboard plugs in beside the USB cable (low enough for its shield tab to clear U1's pins), C1 next to it; M3 holes in the corners, clear of the modules.
- Rules: clearance 0.2 mm, tracks 0.25 mm; net class Power (+5V, +3V3, GND) 0.5 mm.
- To route: PS2_CLK/PS2_DAT (U1.1/U1.2 to U2 LV1/LV2), KBD_CLK/KBD_DAT (U2 HV1/HV2 to
  J3 pins 5 (CLK) and 1 (DATA)), +5V from U1.21 to U2 HV, C1 and J3 pin 4, +3V3 from
  U1.19 (or U1.36) to U2 LV, GND from U1.20/U1.22 to U2's two GNDs, C1, J3 pin 3 and its
  three shield tabs. A GND pour on the bottom layer
  suits it.

What it is based on:

## The module (from Sipeed's v3921 dimension drawing and v3923 schematic)

- Board 54.04 × 22.55 mm; two rows of 20 pins, 2.54 mm pitch, **20.32 mm apart**
  (centre to centre); the first pin about 2.6 mm from the USB end.
- Left header (module J6), pin 1 at the USB end: FPGA 73, 74, 75, 85, 77, 15, 16, 27,
  28, 25, 26, 29, 30, 31, 17, 20, 19, 18, 3V3, GND.
- Right header (module J5), pin 1 at the USB end: 5V, GND, 76, 80, 42, 41, 56, 54, 51,
  48, 55, 49, 86, 79, GND, 3V3, 72, 71, 53, 52.
- Seen from above with the USB end on the left, the left header is the bottom row.
- PS/2: clock FPGA 73 (J6 pin 1), data FPGA 74 (J6 pin 2); nothing else on the module
  is wired to them. 52/53 are avoided: they are the HDMI connector's EDID lines.
- The microSD slot is on the module's underside at the USB end, the card going in and
  out at the USB edge: keep that part of the carrier free of tall parts and the card's
  path clear.
- (The v3920 bottom render labels some USB-end pins differently; the schematic and the
  pinout image agree, and are what this uses.)

## Contents

| Ref | Part | Footprint |
|---|---|---|
| U1 | Sipeed Tang Nano 20K (pins 1-20: left header J6, 21-40: right header J5) | `TurboACE:TangNano20K` (kicad/lib), locked |
| J1, J2 | 1×20 female header, 2.54 mm, for the module: BoM only (U1's footprint has the pads) | (`Connector_PinSocket_2.54mm:PinSocket_1x20_P2.54mm_Vertical`) |
| J3 | PS/2 socket: 6-pin mini-DIN female, right angle, shielded, Mauser 011-0716 (pins as the Same Sky MD-60S); 1 DATA, 3 GND, 4 +5V, 5 CLK, shield to GND; front face on the USB edge | `TurboACE:MiniDIN6_PS2_Female` (kicad/lib) |
| U2 | Gebildet 4-channel BSS138 level shifter (SparkFun BOB-12009 circuit), soldered on its two 6-pin headers, labelled side up: channel 1 clock, 2 data, 3-4 unused; LV +3V3, HV +5V; 10 kΩ pull-ups on the module | `TurboACE:LevelShifter_BSS138_4ch_Gebildet` (kicad/lib) |
| C1 | 100 nF ceramic, leaded, 5 mm lead spacing: +5V to GND near J3 | `Capacitor_THT:C_Disc_D5.0mm_W2.5mm_P5.00mm` |
| H1–H4 | M3 mounting holes, clear of the USB/microSD end | `MountingHole:MountingHole_3.2mm_M3` |

Nets: +5V (U1.21), GND (U1.20, U1.22, U1.35), +3V3 (U1.19, U1.36), PS2_CLK (U1.1,
IO73), PS2_DAT (U1.2, IO74) to U2 LV1/LV2, KBD_CLK, KBD_DAT from U2 HV1/HV2 to J3; U2 LV +3V3, HV +5V;
every other module pin no-connect.

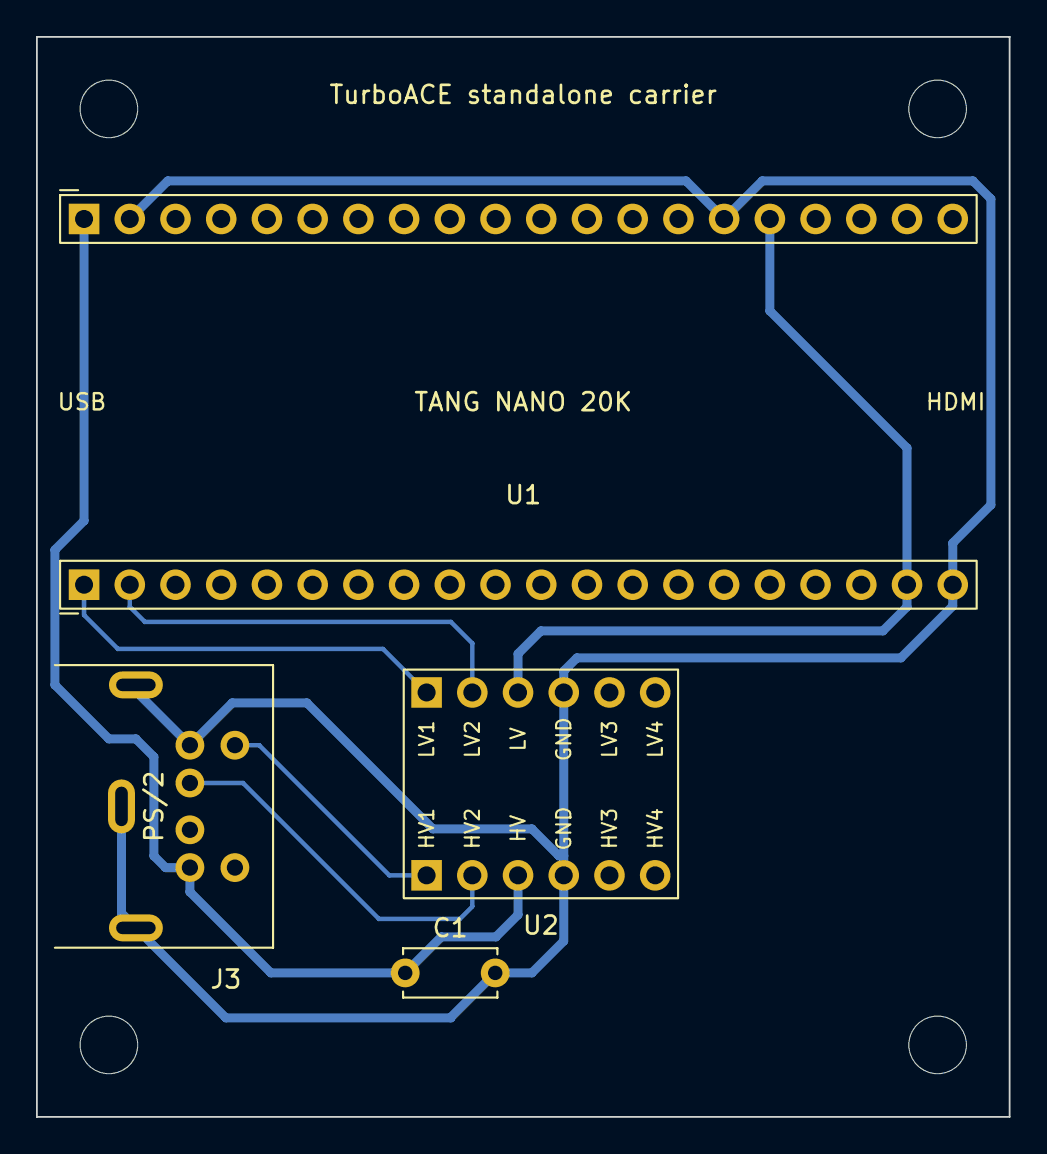
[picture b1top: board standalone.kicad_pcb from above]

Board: 2 copper layers, 54.0 x 60.0 mm, 8 parts (0 on the bottom side), 7 nets.

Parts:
C1: 100n; C_Disc_D5.0mm_W2.5mm_P5.00mm
H1, H2, H3, H4: MountingHole; MountingHole_3.2mm_M3
J3: PS/2 socket; MiniDIN6_PS2_Female
U1: TangNano20K
U2: Level shifter 4ch BSS138; LevelShifter_BSS138_4ch_Gebildet

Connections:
+3V3: U1.19, U1.36, U2.3
+5V: C1.1, J3.4, U1.21, U2.9
/KBD_CLK: J3.5, U2.7
/KBD_DAT: J3.1, U2.8
/PS2_CLK: U1.1, U2.1
/PS2_DAT: U1.2, U2.2
GND: C1.2, J3.3, J3.SH, U1.20, U1.22, U1.35, U2.4, U2.10

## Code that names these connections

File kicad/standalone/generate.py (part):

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    sch.wire(e('U1', '2'), (170.18, dat_y), e('U2', L('LV2')))
    sch.wire(e('U2', L('HV1')), (121.92, clk_y), e('J3', '5'))
    sch.wire(e('U2', L('HV2')), (124.46, dat_y), e('J3', '1'))
    sch.label('PS2_CLK', 172.72, clk_y)
    sch.label('PS2_DAT', 170.18, dat_y)
    sch.label('KBD_CLK', 121.92, clk_y)
    sch.label('KBD_DAT', 124.46, dat_y)
    # U2's supplies, sideways out of its sides (LV and HV are just below the signal
    # wires): the LV side faces U1 (right), the HV side J3 (left); both GNDs down
    for name, side, net, a, d in (('LV', None, '+3V3', 0, 5.08), ('HV', None, '+5V', 180, -5.08),
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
